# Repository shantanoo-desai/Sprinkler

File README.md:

# Sprinkler

An efficient IPv6 Multicast Protocol for distributing data over a wireless network.

It uses:

1. [__Luby-Transform Codes__](https://en.wikipedia.org/wiki/Luby_transform_code)
2. [__Trickle Algorithm__](https://tools.ietf.org/html/rfc6206)

## Usability over

* __802.11 WLAN ad-hoc networks with Raspberry Pis and GNU/Linux computers__

## Usage

__Case__:

    python3 Sprinkler.py
    --version 1 --path /path/to/dir/
    --filename file_to_send --group ff32::2
    --port 30002

will distribute the file `/path/to/dir/file_to_send` over the wireless ad-hoc network Nodes
which are running the same code but will lower `version` number (for instance __0__).
 The `/path/to/dir` will also store all new incoming files.

General:
```
usage: Sprinkler.py [-h] [-V VERSION] [-b BLOCK] [-pt PATH] [-f FILENAME]
                [-g GROUP] [-p PORT]

Sprinkler Wireless Data Dissemination Protocol

optional arguments:
-h, --help            show this help message and exit
-V VERSION, --version VERSION
                    Version Number for Updated Data
-b BLOCK, --block BLOCK
                    Encoding Block Length, keep it less than 1500B
-pt PATH, --path PATH
                    Path to the file for Dissemination / storing Incoming
                    file over channel. Default is
                    current_folder/transmissions
-f FILENAME, --filename FILENAME
                    Main File for Fountain. provide complete path
-g GROUP, --group GROUP
                    IPv6 Multicast Group. Default is ff02::1
-p PORT, --port PORT  port number. Default is 30001

```

### Setup

    sudo ./setup.sh

This file will:

* Check for `python3` and `pip3`

* install the `lt-code` pip module

* make necessary folders for the API and relevant dummy files for default operation

* creates `routeTable.json` for storing information of nearby neighbors and source of information `fountain`

## Application

* Currently being used in [TWIN Testbed](https://github.com/ComNets-Bremen/TWIN) at the [Sustainable Communication Networks, University of Bremen, Germany](http://comnets.uni-bremen.de) to distribute firmware over __802.11 WLAN back-channel__

## Dependencies

It uses [LT-Code Github Repository by Anson Rosenthal](https://github.com/anrosent/lt-code)

install `pip3` module first using:

    sudo pip3 install lt-code

## References

[Complete Report of the Protocol at ResearchGate](http://dx.doi.org/10.13140/RG.2.2.32561.99687)

### License

published under __GNU Public License v3 (GPLv3)__

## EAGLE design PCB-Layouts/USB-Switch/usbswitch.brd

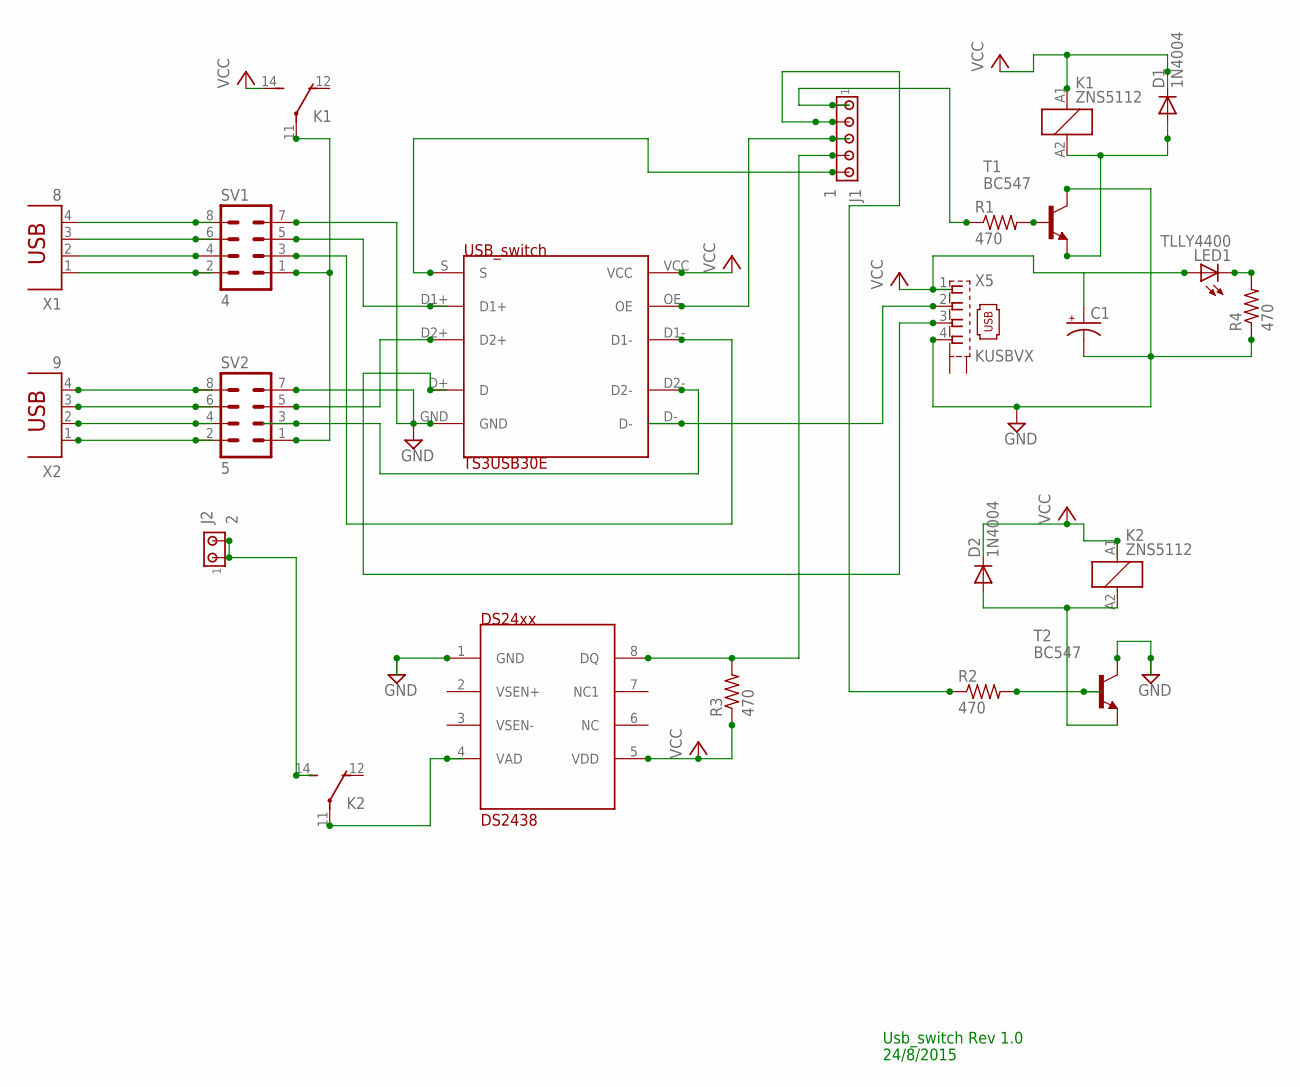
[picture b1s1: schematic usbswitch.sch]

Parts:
C1: CPOL-USB45181A; B45181A
D1, D2: 1N4004; DO41-10
J1: 1; 10X05MTA
J2: 2; 1X2MTA
K1, K2: ZNS5112; ZN5
LED1: TLLY4400; LED3MM
R1, R2, R3, R4: 470; 0204/5
SV1: 4; MA04-2
SV2: 5; MA04-2
T1, T2: BC547; TO92
U$1: USB_SWITCH; PDSO-G10
U$2: DS2438; DS243PKG
X1: 8; PN87520
X2: 9; PN87520
X5: KUSBVX

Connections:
GND: C1.-, R4.1, SV1.7, SV2.7, T1.3 (C), T2.3 (C), U$1.GND, U$2.1 (GND), X5.4
unnamed: SV1.8, X1.4
unnamed: SV1.6, X1.3
unnamed: SV1.4, X1.2
unnamed: J1.5, U$1.S
unnamed: SV2.8, X2.4
unnamed: SV2.6, X2.3
unnamed: SV2.4, X2.2
unnamed: R1.2, T1.2 (B)
unnamed: SV1.5, U$1.D1+
unnamed: SV1.3, U$1.D1-
unnamed: SV2.5, U$1.D2+
unnamed: SV2.3, U$1.D2-
unnamed: D1.A, K1.A2 (2), T1.1 (E)
unnamed: J1.3, U$1.OE
unnamed: U$1.D-, X5.2
unnamed: U$1.D+ (D), X5.3
unnamed: J1.1, R1.1
unnamed: J1.4, R3.2, U$2.8 (DQ)
unnamed: K2.11, U$2.4 (VAD)
unnamed: LED1.K (C), R4.2
unnamed: SV1.2, X1.1
unnamed: SV2.2, X2.1
unnamed: K1.11, SV1.1, SV2.1
unnamed: J2.1, J2.2, K2.14 (S)
unnamed: J1.2, R2.1
unnamed: D2.A, K2.A2 (2), T2.1 (E)
unnamed: R2.2, T2.2 (B)
VCC: C1.+, D1.C, D2.C, K1.14 (S), K1.A1 (1), K2.A1 (1), LED1.A, R3.1, U$1.VCC, U$2.5 (VDD), X5.1

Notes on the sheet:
Usb_switch Rev 1.0
24/8/2015

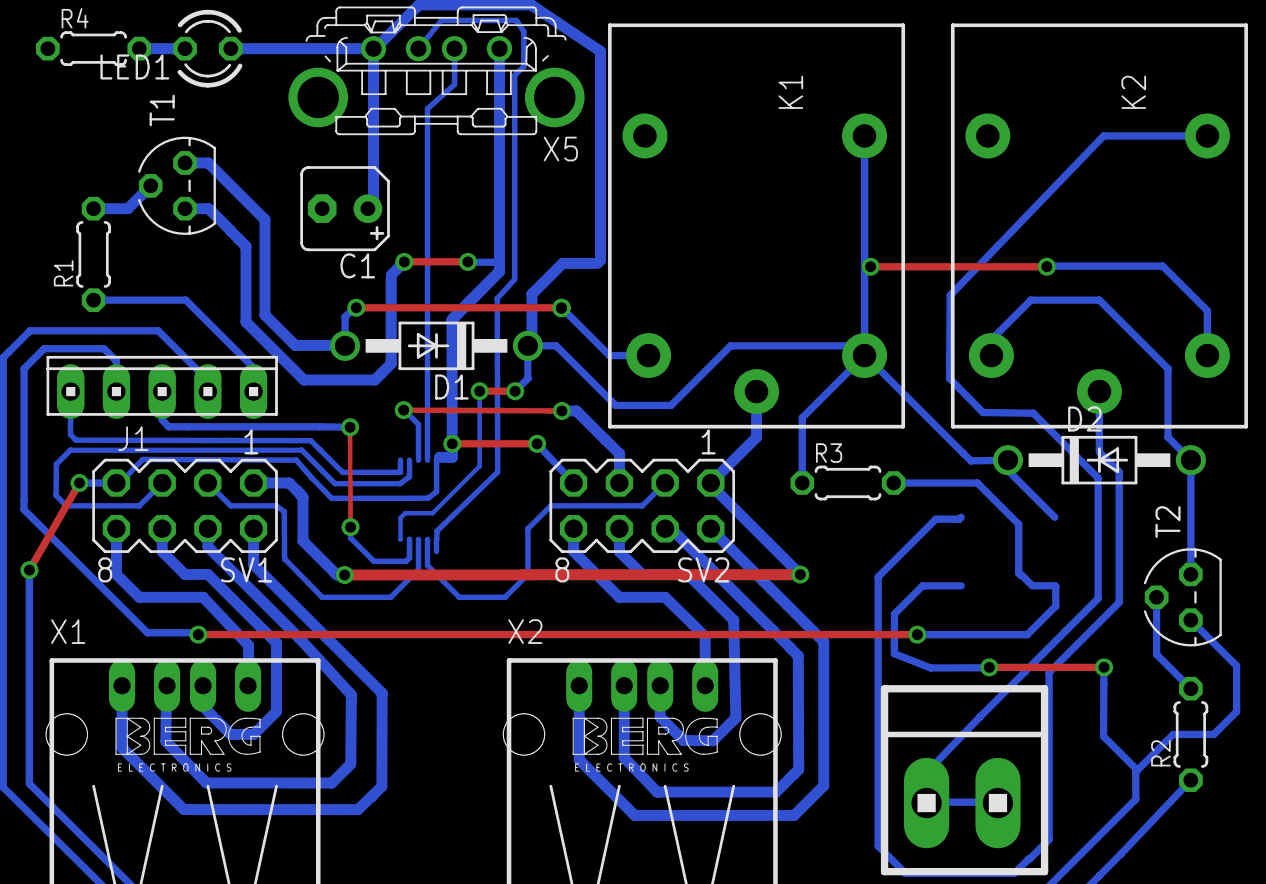
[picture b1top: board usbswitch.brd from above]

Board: 2 copper layers, 21 parts (1 on the bottom side), 29 nets.

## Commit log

2016-04-05 Initial Commit: 5/4/2016
2016-04-05 Commit: 5/4/2016
2016-04-05 More comments Commit: 5/4/2016
2016-04-06 Added Version Control
2016-04-06 More spec 6/4/2016
2016-04-14 Cleanup Before Branching
2016-04-29 Added Pi install, removed sleep
2016-04-30 Changes to make this work!
    - Don't need to bind the server socket
    - Instantiate an LtDecoder for the Receiver, use the 'consume_block' API
    - Pass file-like BytesIO wrapper around received data so we can parse it
    into an LT block using the existing stream API
    - Print the decoded file when done!
2016-05-01 Added License
2016-05-01 Added ACM link and Paper ref
2016-05-02 Added USB-switch Schematics
2016-05-07 Version: 2.0
2016-05-07 Added Description
2016-05-07 changes tabs to spaces acc. to PEP8
2016-05-12 Added Timeout and Example
2016-05-12 Improvement
2016-05-20 Version Improvement 2.0
2016-05-22 Version 2.1 w/ Trickle
2016-05-22 Version:2.1 cleanup
2016-05-22 V.2.1 Update
2016-05-22 V.2.1 Cleanup
2016-05-22 V2.1 Cleanup
2016-05-23 Fountain restart and bucket change
2016-05-24 Trickle Consistent check
2016-05-25 Updates: 25thMay16
2016-05-26 added License tag & Wiki
2016-05-26 License added
2016-06-07 changes for RT scenario
2016-06-07 change in readme
2016-06-07 no timeout, mdns name add, optimum trickleParams
2016-06-13 solved the socket.herror
2016-06-13 Clean before refactor
2016-06-13 Refactor code:v1
2016-06-13 Refactor: added ttimer
2016-06-14 Threading added
2016-06-15 before merge
2016-06-16 Refactor Bucket
2016-06-17 Added Updates
2016-06-17 added Logger on socket
2016-06-26 Stable code/ v.3
2016-06-27 v3.0 python3.2 compatible thread in fountain
2016-06-27 python3.2 thread compatibility for RPis
2016-06-30 removed Notification message
2016-07-04 some conflict in fountain resolved
2016-07-04 more glitches solved
2016-07-04 resolved problems in fountain
2016-07-04 tests:1 parameter change
2016-07-04 devl: added comment
2016-08-12 CleanUp of Old Code
2016-08-12 V0.1 -- Initial README
2016-08-15 Added Stable Code: v0.1
2016-08-15 Added new help & Description:v0.1
2016-08-16 This makes things more silent in BackChannel: v0.1.1
2016-08-16 File placement glitch:v0.1.1
2016-08-16 Counter Problem:v0.1.1
2016-08-18 added missing handler/formatter for logging: Data logs now v.0.1.1
2016-08-19 Routing Table in JSON:v0.2
2016-08-22 consumption counter added:v2.0.1
2016-08-29 Major Bug with Gamma Formula resolved: v2.0.1
2016-08-30 minor changes : v2.0.1
2017-03-22 v3.0 Major Refactor/Cleanup
2017-03-22 v3.0 improved README
2017-03-23 v3.0 added travis-ci + test script
2017-03-23 remove CI
2017-03-23 v3.0 quick hotfix README
2017-03-23 v3.0 routeTable generation and save fix
2017-03-24 added necessary PATH for incoming/outgoing files
2017-03-24 add setup for incoming/outgoing folder in setup script
2017-03-24 ignore folders and file created from setup script
2017-03-24 added more Description for Path variable
2017-03-24 resolved error forPATH and FILENAME
2017-03-24 default filename error resolved
2017-03-24 removed redundant JSON file creating from setup
2017-03-24 removed change_dir command from modules to avoid API crash
2017-03-27 Add Time Logging functionality
